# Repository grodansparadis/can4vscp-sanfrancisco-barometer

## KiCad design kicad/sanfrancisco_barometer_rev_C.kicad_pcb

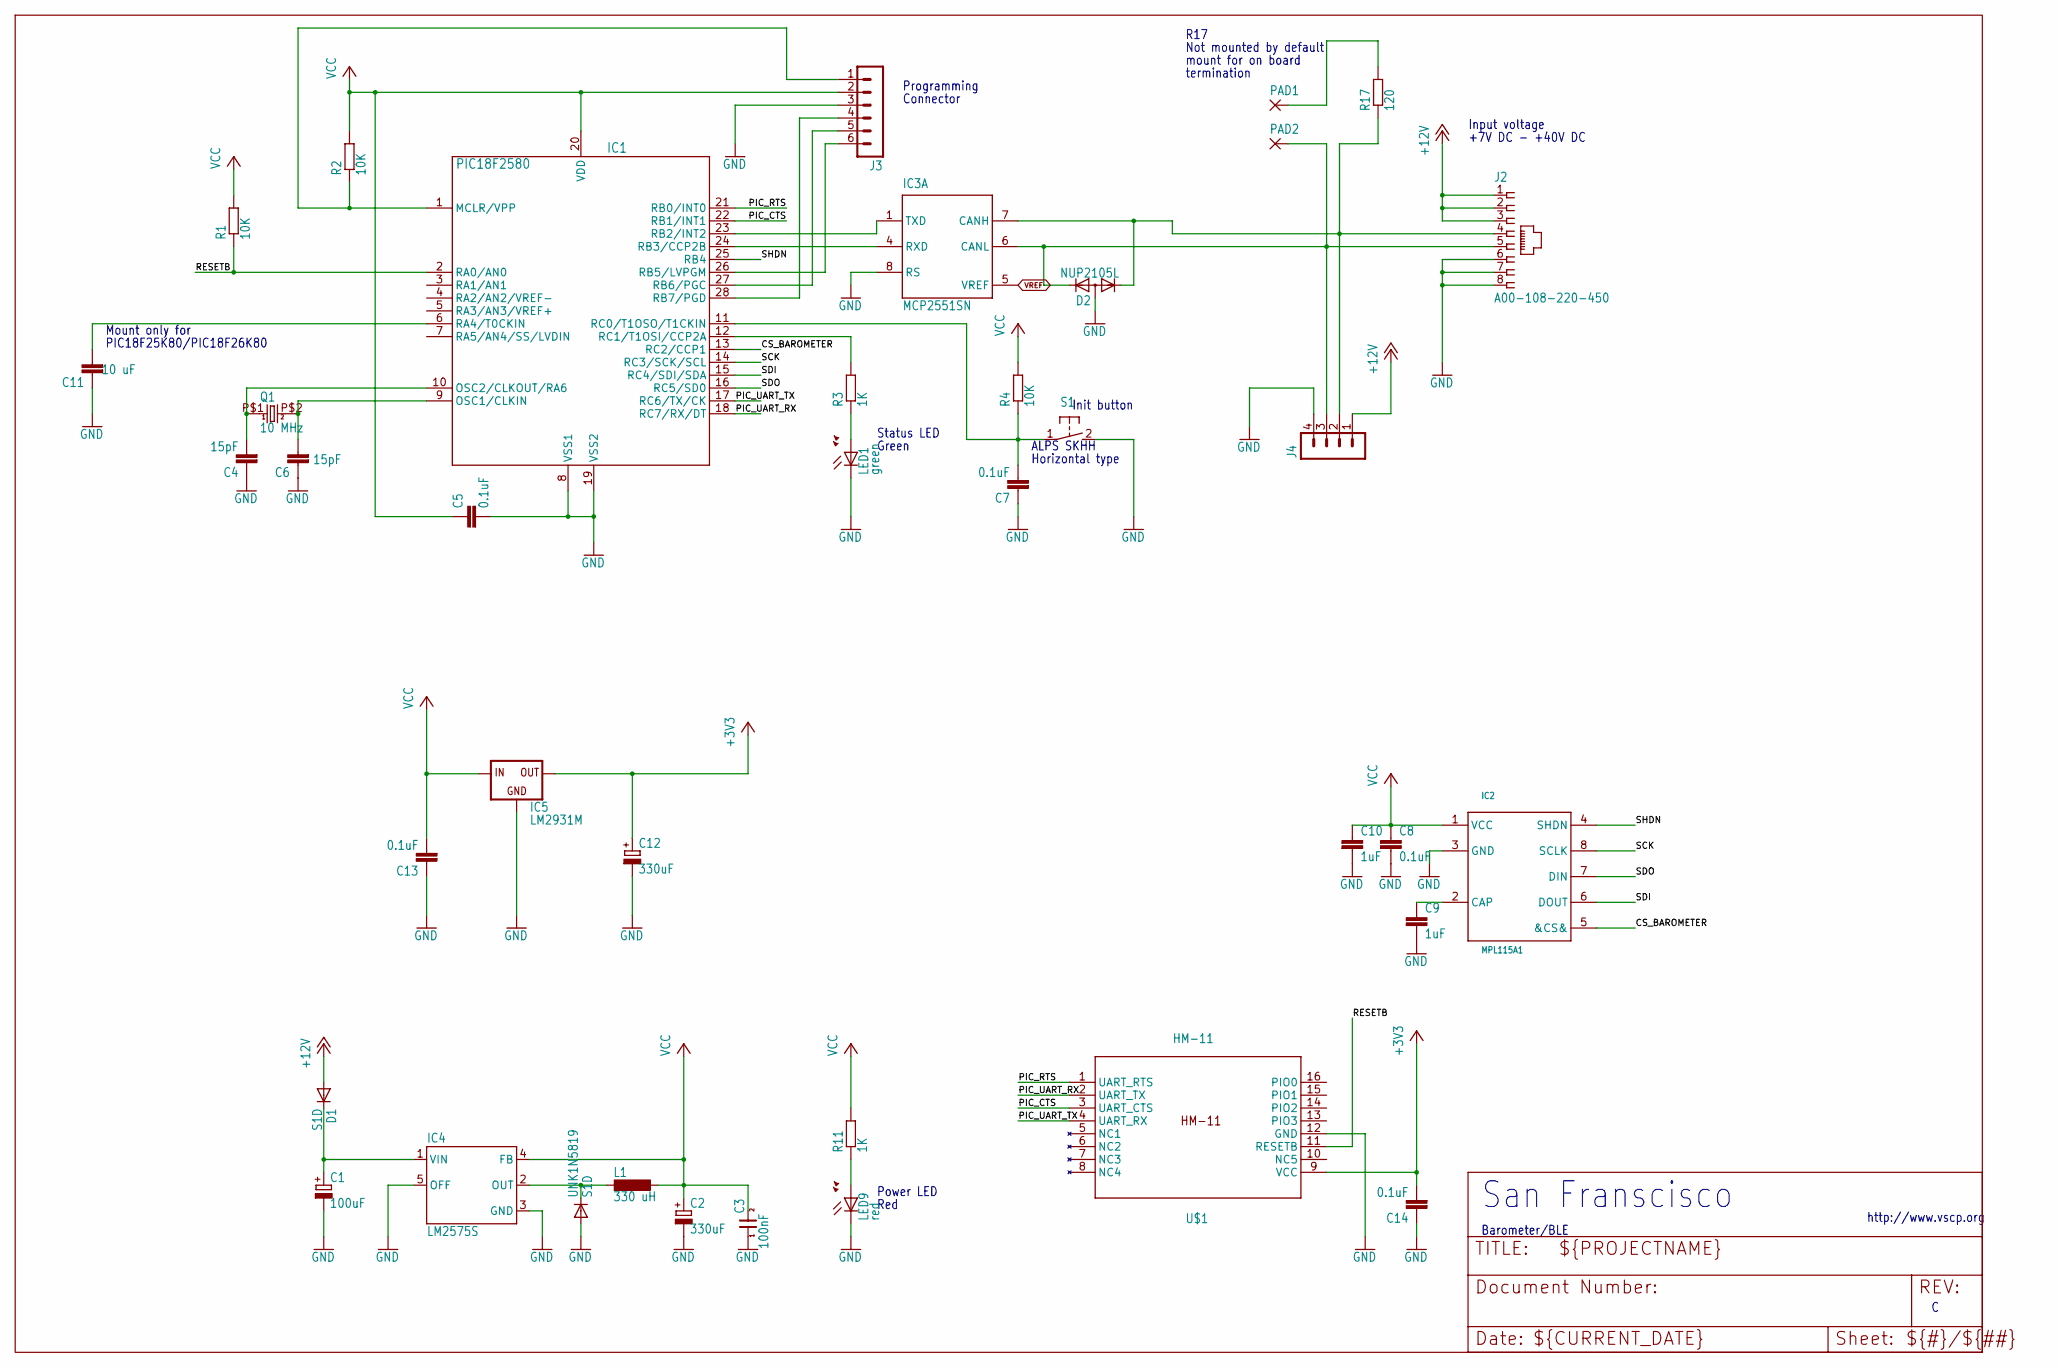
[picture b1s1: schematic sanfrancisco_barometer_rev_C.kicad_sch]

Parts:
C1: 100uF; PANASONIC_D
C2, C12: 330uF; PANASONIC_D
C3: 100nF; 0805
C4, C6: 15pF; C0805
C5, C7, C8, C13, C14: 0.1uF; C0805
C9, C10: 1uF; C0805
C11: 10 uF; C0805
D1: S1D; SOD123
D2: NUP2105L; SOT23
IC1: PIC18F2580; SO28
IC2: MPL115A1; LGA8
IC3: MCP2551SN; SO-08
IC4: LM2575S; TO263-5
IC5: LM2931M; SO08
J2: A00-108-220-450; RJ-45
J3: MA06-1
J4: MA04-1
L1: 330 uH; DO3316P
LED1: green; CHIP-LED0805
LED9: red; CHIP-LED0805
PAD1, PAD2: 1,6/0,8; 1,6_0,8
Q1: 10 MHz; 9C
R1, R2, R4: 10K; R0805
R3, R11: 1K; R0805
R17: 120; R0805
S1: 31-XX; B3F-31XX
U$1: HM-11
UNK1N5819: S1D; SOD123

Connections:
+3V3: C12.+, C14.2, IC5.1 (OUT), U$1.9 (VCC)
+12V: D1.A, J2.1, J2.2, J2.3, J4.1
CANL: D2.2 (K2), IC3.6 (CANL), J2.5, J4.3, PAD2.1
CS_BAROMETER: IC1.13 (RC2/CCP1), IC2.5 (&CS&)
GND: C1.-, C2.-, C3.1, C4.1, C5.2, C6.1, C7.1, C8.2, C9.2, C10.2, C11.1, C12.-, C13.1, C14.1, D2.3 (A), IC1.8 (VSS1), IC1.19 (VSS2), IC2.3 (GND), IC3.2 (VSS), IC3.8 (RS), IC4.3 (GND), IC4.5 (OFF), IC5.2 (GND), J2.6, J2.7, J2.8, J3.3, J4.4, LED1.C, LED9.C, S1.2 (S), U$1.12 (GND), UNK1N5819.A
unnamed: IC4.2 (OUT), L1.1, UNK1N5819.C
unnamed: C4.2, IC1.10 (OSC2/CLKOUT/RA6), Q1.P$1 (1)
unnamed: C1.+, D1.C, IC4.1 (VIN)
unnamed: IC1.12 (RC1/T1OSI/CCP2A), R3.2
unnamed: LED1.A, R3.1
unnamed: C7.2, IC1.11 (RC0/T1OSO/T1CKIN), R4.1, S1.1
unnamed: C6.2, IC1.9 (OSC1/CLKIN), Q1.P$2 (2)
unnamed: C11.2, IC1.6 (RA4/T0CKIN)
unnamed: C9.1, IC2.2 (CAP)
unnamed: IC1.1 (MCLR/VPP), J3.1, R2.1
unnamed: IC1.28 (RB7/PGD), J3.4
unnamed: IC1.27 (RB6/PGC), J3.5
unnamed: IC1.26 (RB5/LVPGM), J3.6
unnamed: PAD1.1, R17.2
unnamed: LED9.A, R11.1
unnamed: D2.1 (K1), IC3.7 (CANH), J2.4, J4.2, R17.1
PIC_CTS: IC1.22 (RB1/INT1), U$1.3 (UART_CTS)
PIC_RTS: IC1.21 (RB0/INT0), U$1.1 (UART_RTS)
PIC_UART_RX: IC1.18 (RC7/RX/DT), U$1.2 (UART_TX)
PIC_UART_TX: IC1.17 (RC6/TX/CK), U$1.4 (UART_RX)
RESETB: IC1.2 (RA0/AN0), R1.1, U$1.11 (RESETB)
RXCAN: IC1.24 (RB3/CCP2B), IC3.4 (RXD)
SCK: IC1.14 (RC3/SCK/SCL), IC2.8 (SCLK)
SDI: IC1.15 (RC4/SDI/SDA), IC2.6 (DOUT)
SDO: IC1.16 (RC5/SD0), IC2.7 (DIN)
SHDN: IC1.25 (RB4), IC2.4 (SHDN)
TXCAN: IC1.23 (RB2/INT2), IC3.1 (TXD)
VCC: C2.+, C3.2, C5.1, C8.1, C10.1, C13.2, IC1.20 (VDD), IC2.1 (VCC), IC3.3 (VDD), IC4.4 (FB), IC5.8 (IN), J3.2, L1.2, R1.2, R2.2, R4.2, R11.2
VREF: IC3.5 (VREF)

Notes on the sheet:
Horizontal type
termination
Input voltage
Status LED
Green
mount for on board
http://www.vscp.org
Mount only for
Connector
R17
Power LED
Init button
Programming
ALPS SKHH
Not mounted by default
Red
Barometer/BLE
+7V DC - +40V DC
PIC18F25K80/PIC18F26K80
San Franscisco

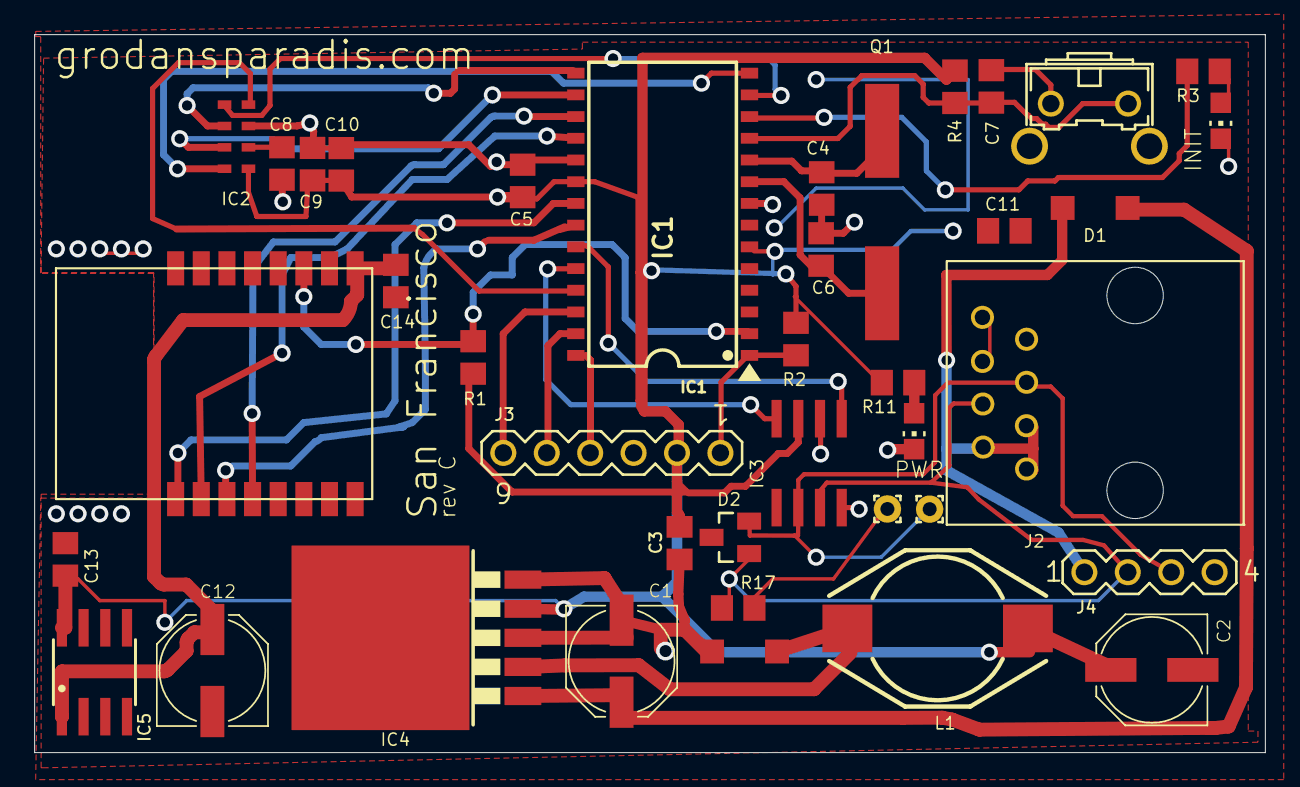
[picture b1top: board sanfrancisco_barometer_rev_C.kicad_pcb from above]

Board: 6 copper layers, 72.0 x 42.0 mm, 39 parts (0 on the bottom side), 33 nets.

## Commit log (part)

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2025-08-18 Converted schema to kicad
2025-09-30 Changed license to MIT
2026-05-05 Updated license to CERN
